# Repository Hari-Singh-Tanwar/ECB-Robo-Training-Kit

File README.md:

# ECB Robo Training Kit
Cadlab [[https://cadlab.io/project/29749/master/files]]

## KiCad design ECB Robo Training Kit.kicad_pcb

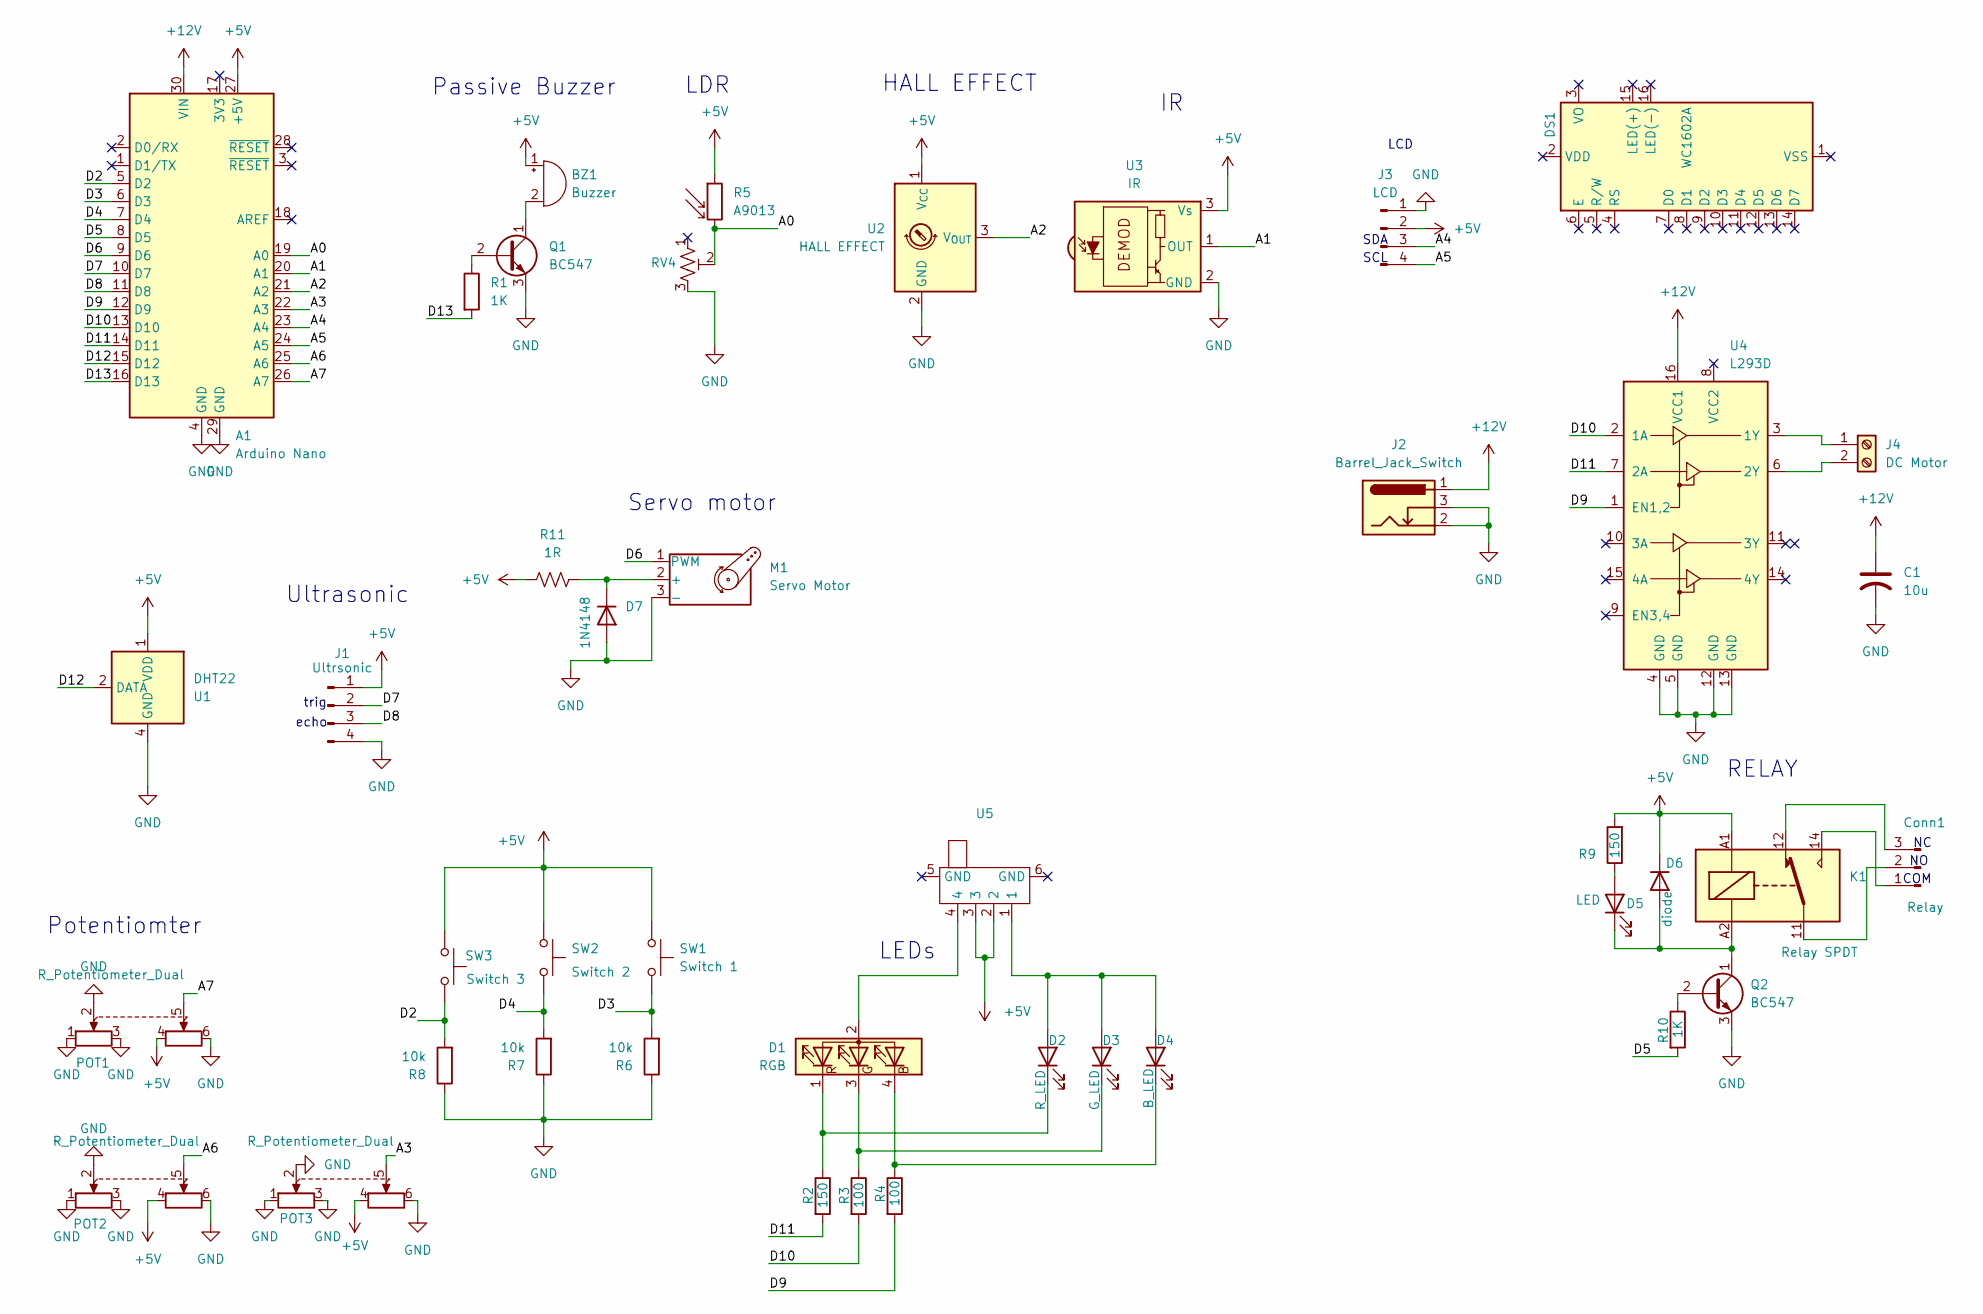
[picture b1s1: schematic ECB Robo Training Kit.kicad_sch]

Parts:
A1: Arduino Nano; Arduino_Nano
BZ1: Buzzer; Buzzer_12x9.5RM7.6
C1: 10u; C_Radial_D6.3mm_H11.0mm_P2.50mm
Conn1: Relay; TerminalBlock_Phoenix_MKDS-1,5-3-5.08_1x03_P5.08mm_Horizont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
D1: RGB; LED_D5.0mm-4_RGB_Wide_Pins
D2: R_LED; LED_D5.0mm
D3: G_LED; LED_D5.0mm
D4: B_LED; LED_D5.0mm
D5: LED; LED_D5.0mm
D6: diode; D_DO-15_P12.70mm_Horizontal
D7: 1N4148; D_DO-35_SOD27_P7.62mm_Horizontal
DS1: WC1602A
J1: Ultrsonic; PinHeader_1x04_P2.54mm_Vertical
J2: Barrel_Jack_Switch; BarrelJack_Horizontal
J3: LCD; PinHeader_1x04_P2.54mm_Vertical
J4: DC Motor; TerminalBlock_Phoenix_MKDS-1,5-2-5.08_1x02_P5.08mm_Horizont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
K1: Relay SPDT; Relay_SPDT_Finder_36.11
M1: Servo Motor; PinHeader_1x03_P2.54mm_Horizontal
POT1, POT2, POT3: R_Potentiometer_Dual; Potentiometer_Alps_RK163_Dual_Horizontal
Q1, Q2: BC547; TO-92_Wide
R1, R10: 1K; R_Axial_DIN0207_L6.3mm_D2.5mm_P10.16mm_Horizontal
R2, R9: 150; R_Axial_DIN0207_L6.3mm_D2.5mm_P10.16mm_Horizontal
R3, R4: 100; R_Axial_DIN0207_L6.3mm_D2.5mm_P10.16mm_Horizontal
R5: A9013; R_LDR_7x6mm_P5.1mm_Vertical
R6, R7, R8: 10k; R_Axial_DIN0207_L6.3mm_D2.5mm_P10.16mm_Horizontal
R11: 1R; R_Axial_DIN0204_L3.6mm_D1.6mm_P7.62mm_Horizontal
RV4: R_Potentiometer_Trim_US; Potentiometer_Runtron_RM-065_Vertical
SW1: Switch 1; SW_PUSH-12mm
SW2: Switch 2; SW_PUSH-12mm
SW3: Switch 3; SW_PUSH-12mm
U1: DHT22; Aosong_DHT11_5.5x12.0_P2.54mm
U2: HALL EFFECT; TO-92Flat
U3: IR; Vishay_MOLD-3Pin
U4: L293D; DIP-16_W7.62mm
U5: 1P3T_Slide_Switch

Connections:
+5V: A1.27 (+5V), BZ1.1 (+), D6.1 (K), J1.1, J3.2, K1.A1, POT1.4, POT2.4, POT3.4, R5.1, R9.2, R11.1, SW1.1, SW2.1, SW3.1, U1.1 (VDD), U2.1 (V_{CC}), U3.3 (Vs), U5.2, U5.3; also elsewhere on the board
+12V: A1.30 (VIN), C1.1, J2.1, U4.16 (VCC1)
/A0: A1.19 (A0), R5.2, RV4.2
/A1: A1.20 (A1), U3.1 (OUT)
/A2: A1.21 (A2), U2.3 (V_{OUT})
/A3: A1.22 (A3), POT3.5
/A4: A1.23 (A4), J3.3
/A5: A1.24 (A5), J3.4
/A6: A1.25 (A6), POT2.5
/A7: A1.26 (A7), POT1.5
/D2: A1.5 (D2), R8.2, SW3.2
/D3: A1.6 (D3), R6.2, SW1.2
/D4: A1.7 (D4), R7.2, SW2.2; also elsewhere on the board
/D5: A1.8 (D5), R10.2
/D6: A1.9 (D6), M1.1 (PWM)
/D7: A1.10 (D7), J1.2
/D8: A1.11 (D8), J1.3
/D9: A1.12 (D9), R4.2, U4.1 (EN1,2)
/D10: A1.13 (D10), R3.2, U4.2 (1A)
/D11: A1.14 (D11), R2.2, U4.7 (2A)
/D12: A1.15 (D12), U1.2 (DATA)
/D13: A1.16 (D13), R1.2
GND: A1.4 (GND), A1.29 (GND), C1.2, D7.2 (A), J1.4, J2.2, J2.3, J3.1, M1.3 (-), POT1.1, POT1.2, POT1.3, POT1.6, POT2.1, POT2.2, POT2.3, POT2.6, POT3.1, POT3.2, POT3.3, POT3.6, Q1.3 (E), Q2.3 (E), R6.1, R7.1, R8.1, RV4.3, U1.4 (GND), U2.2 (GND), U3.2 (GND), U4.4 (GND), U4.5 (GND), U4.12 (GND), U4.13 (GND)
unnamed: BZ1.2 (-), Q1.1 (C)
unnamed: Conn1.1, K1.14
unnamed: Conn1.2, K1.11
unnamed: Conn1.3, K1.12
unnamed: D1.2 (A), U5.4
unnamed: D1.4 (B), D4.1 (K), R4.1
unnamed: D1.3 (G), D3.1 (K), R3.1
unnamed: D1.1 (R), D2.1 (K), R2.1
unnamed: D2.2 (A), D3.2 (A), D4.2 (A), U5.1
unnamed: D5.2 (A), R9.1
unnamed: D5.1 (K), D6.2 (A), K1.A2, Q2.1 (C)
unnamed: D7.1 (K), M1.2 (+), R11.2
unnamed: J4.1, U4.3 (1Y)
unnamed: J4.2, U4.6 (2Y)
unnamed: Q1.2 (B), R1.1
unnamed: Q2.2 (B), R10.1

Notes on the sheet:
trig
Potentiomter
RELAY
SCL
LCD
Ultrasonic
COM
Passive Buzzer
HALL EFFECT
LEDs
Servo motor
SDA
LDR
echo

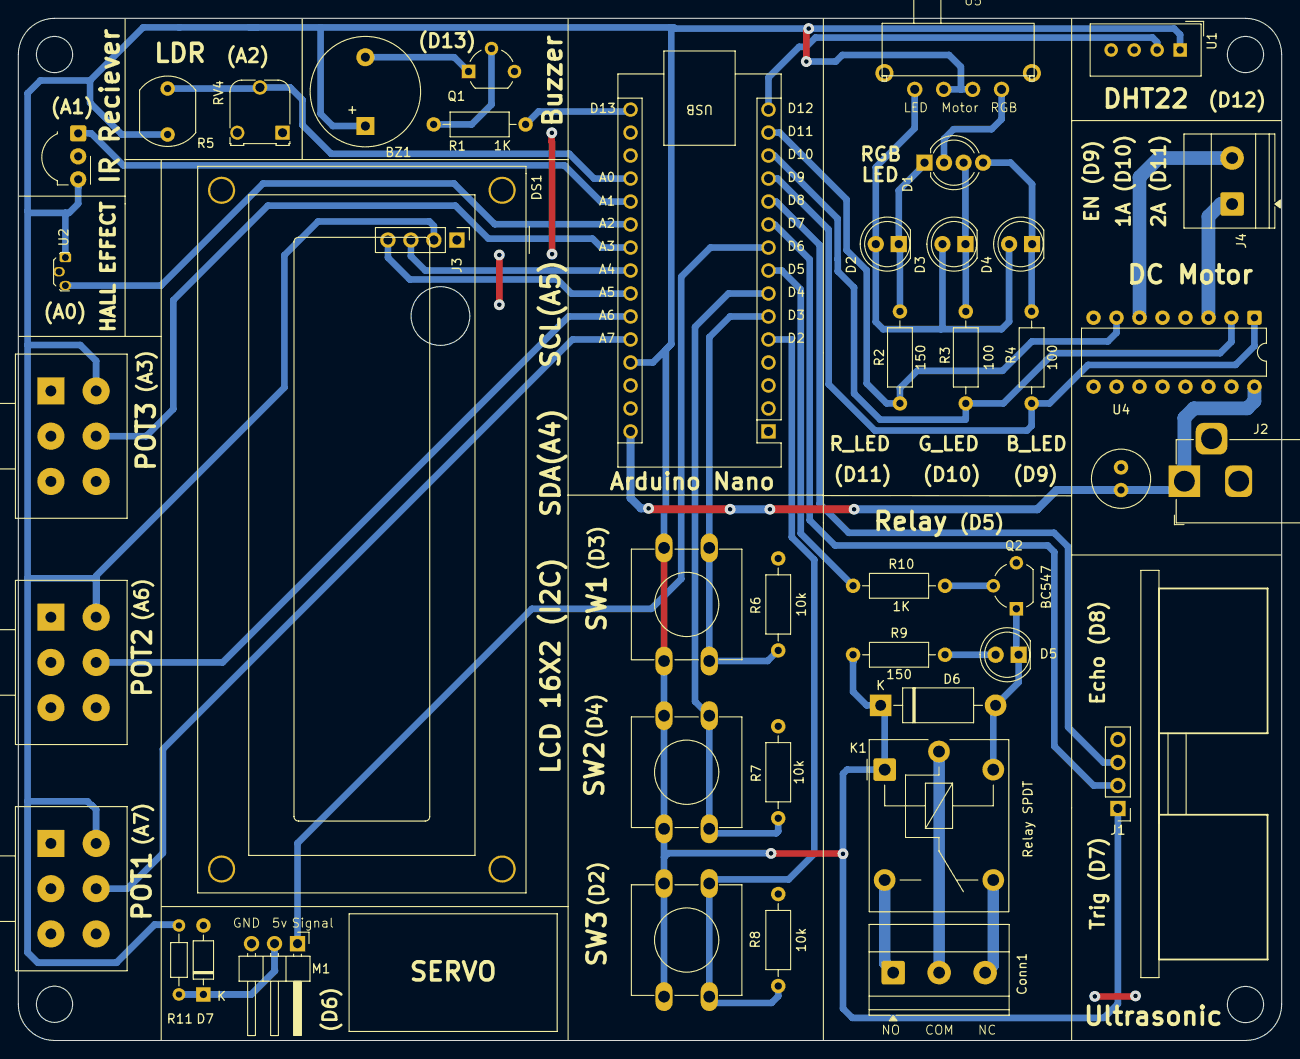
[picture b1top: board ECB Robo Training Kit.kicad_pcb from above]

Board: 2 copper layers, 139.6 x 113.0 mm, 43 parts (0 on the bottom side), 39 nets.

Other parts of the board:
SW2 : Switch 2; SW_PUSH-12mm

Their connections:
+5V: SW2.1; also elsewhere on the board
/D4: SW2.2; also elsewhere on the board

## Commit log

2025-11-14 Version 1
2025-11-14 added link
2026-03-11 Changed the silkscreen and pin a0 and a2. Added 3d models in the PCB
